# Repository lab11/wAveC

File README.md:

wAveC - View AC Current and Voltage Waveforms
=============================================

Often it is useful to simultaneously view the current and voltage waveforms
for a load. Breaking out the high-voltage phase line for attaching an
oscilloscope can be precarious. This device is a simple way to plug in
a load and run BNC cables to a scope to see a real-time view of the
waveforms.

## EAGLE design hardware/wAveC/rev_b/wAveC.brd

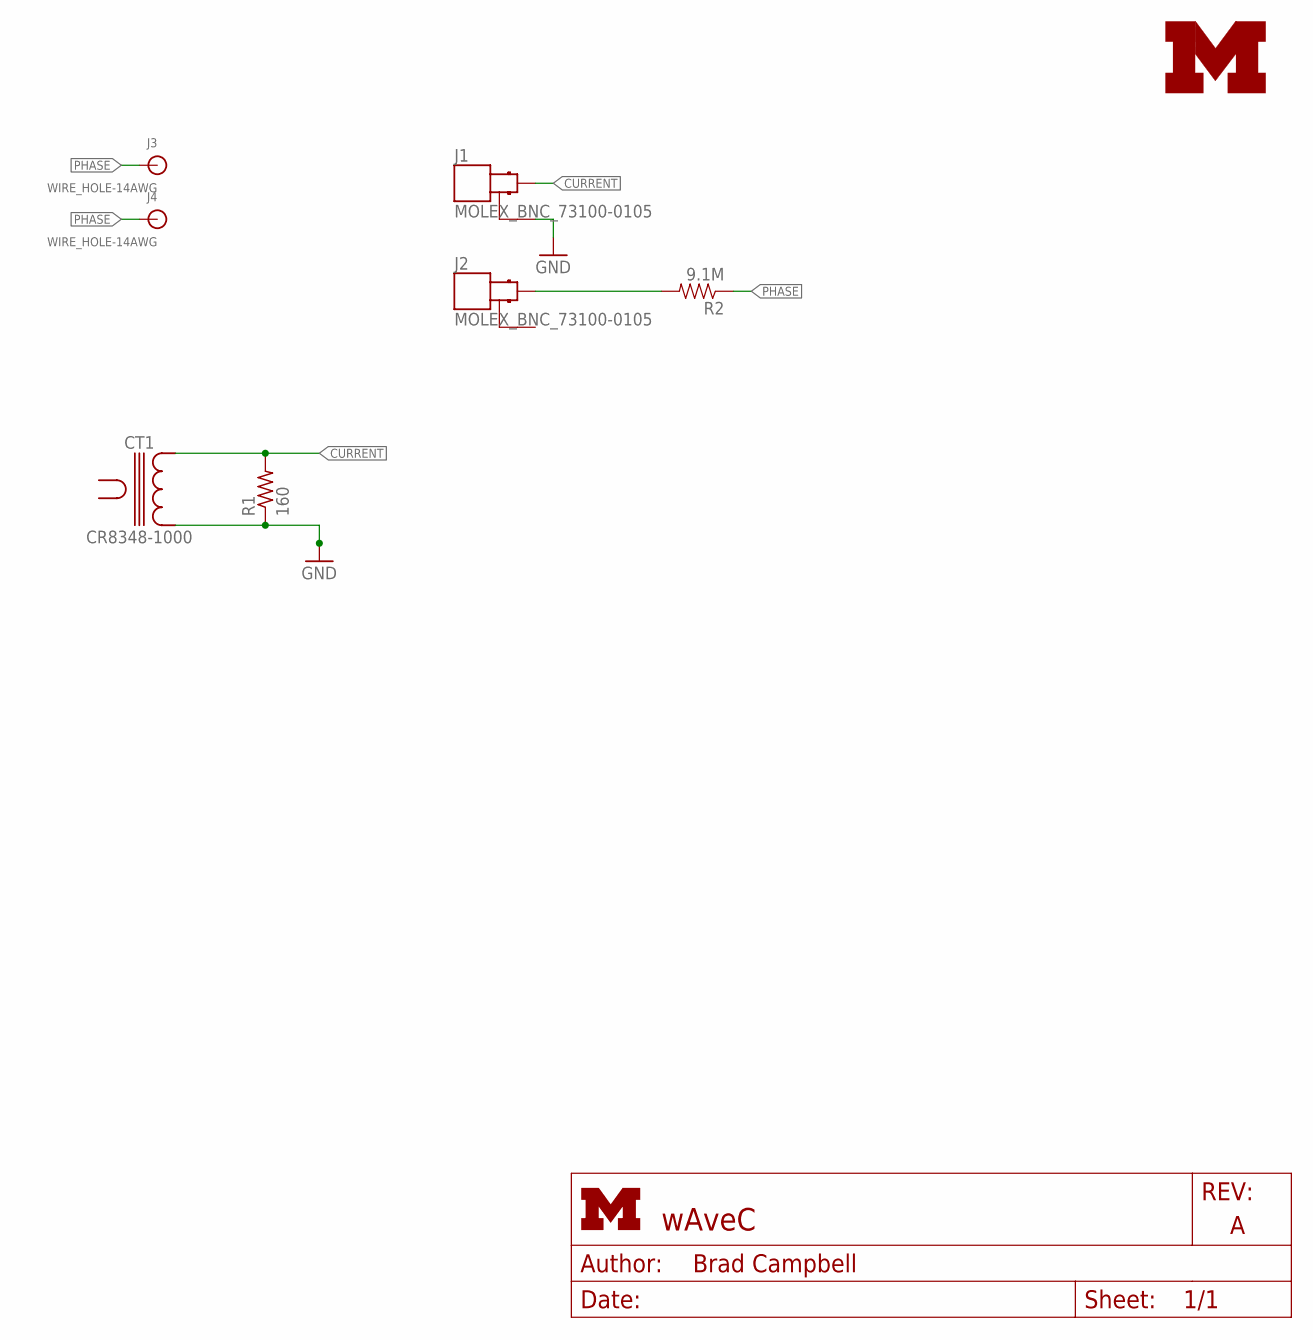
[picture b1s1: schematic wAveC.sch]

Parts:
CT1: CR8348-1000; CR8348
J1, J2: MOLEX_BNC_73100-0105; MOLEX-BNC-73100-0105
J3, J4: WIRE_HOLE-14AWG
LOGO1: UMICH_SOLID_MEDIUM; UMICH_SOLID_200MIL
R1: 160; R1210; DIGIKEY P160QCT-ND
R2: 9.1M; 1206; DIGIKEY 311-9.10MFRCT-ND

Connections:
CURRENT: CT1.1, J1.SIGNAL, R1.2
GND: CT1.2, J1.GND1 (GND), J1.GND2 (GND), R1.1
unnamed: J2.SIGNAL, R2.2
PHASE: J3.P$1, J4.P$1, R2.1

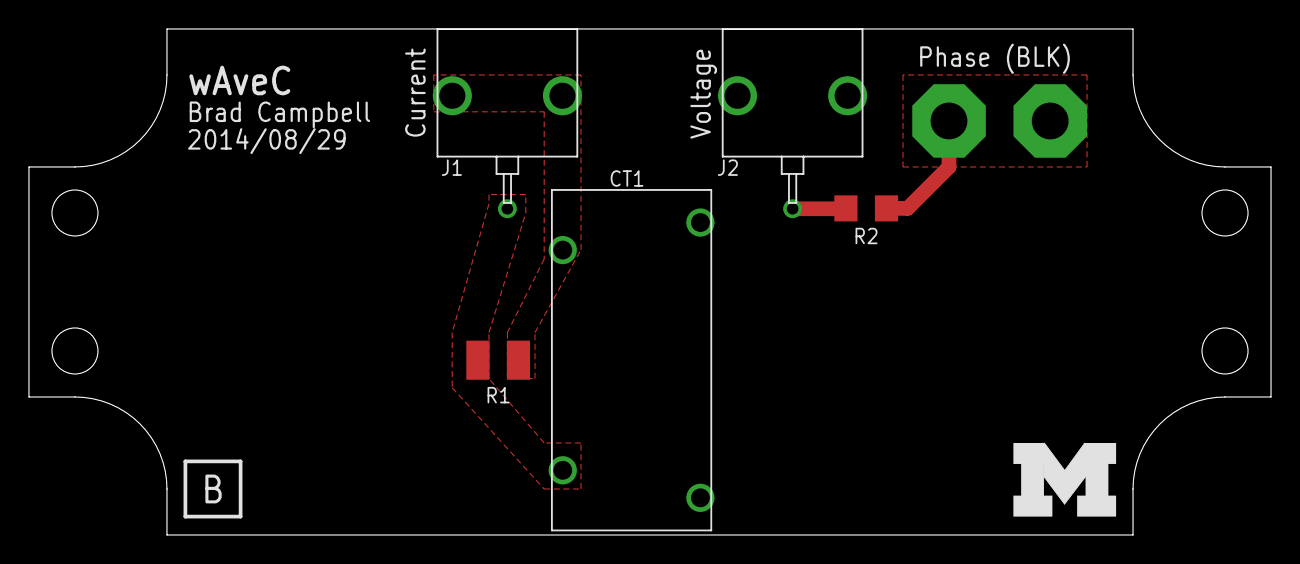
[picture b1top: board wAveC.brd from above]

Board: 2 copper layers, 85.7 x 34.9 mm, 8 parts (0 on the bottom side), 4 nets.

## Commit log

2014-05-18 adding wavec schematic
2014-05-18 added some layout
2014-05-18 wavec routed
2014-05-19 added silkscreen
2014-05-21 added description to readme
2014-06-08 first pass at bottom of case
    created a case bottom and all the pcb parts in cad
2014-06-08 added top to case
    made walls skinnier too
2014-06-08 updated wavec labels and date
2014-06-08 bom + files to ship
2014-06-08 ignores
2014-06-08 updated files for oshpark
2014-06-08 updated gitignore
2014-08-29 wave c with 9 megaohm resistor

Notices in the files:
parts and their libraries:
SparkFun-Resistors: Licensing: CC v3.0 Share-Alike You are welcome to use this library for commercial purposes.
